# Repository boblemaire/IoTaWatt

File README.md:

### IotaWatt 4.8

See the [WiKi](https://github.com/boblemaire/IoTaWatt/wiki) for detailed information concerning installation and use of IoTaWatt. 

IoTaWatt forum is [here](https://community.iotawatt.com/)

IotaWatt is an open-hardware/open-source project to produce an accurate, low-cost, multi-channel, and easy to use electric power monitor.  It's based on the ESP8266 IoT platform using MCP3208 12 bit ADCs to sample voltage and current at high sample rates. As a datalogger the device has a real-time clock and SDcard and supports data querry with the integrated web server.

* monitors up to 14 circuits  
* Accuracy typically within 1%  
* Local SDcard stores up to 15 years worth of data.
* REST APIs to extract data
* Supports many different make, model and capacity current transformers  
* Supports generic definition of any current transformer  
* Three-phase capable  
* Local LAN browser based configuration  
* Local LAN browser based status display  
* Local LAN browser based graphing analytic tools  
* Open Hardware/Software 
* Upload to influxDB   
* Upload to [Emoncms.org](https://emoncms.org/)  
* Demo configuration app at [IoTaWatt.com](http://iotawatt.com)  

The software samples input channels at a rate of 35-40 channels per second, recording voltage(V), power(Watts), and energy(kWh) to the local SD card every five seconds.  The Emoncms browser based graphing utility can be used on the local WiFi network to view data or the data can be uploaded to an Emoncms server or an influxDB server. In the event of WiFi or internet service disruptions, the IotaWatt will continue to log locally and bulk update the server when WiFi is restored.

The basic configuration uses one voltage reference channel and fourteen current sense channels for monitoring up to fourteen single phase circuits.  Current sense channels may be used, with slight modification, as additional voltage/phase reference channels to allow monitoring of three-phase power systems.  There is also an option to estimate three phase power using a single voltage/phase reference.

The configuration and monitoring app runs on any browser based device that is connected to the local WiFi network. A demo is available at [iotawatt.com](http://iotawatt.com)

Thanks to contributors of other open software that have been incorporated into this project.  In particular the Emoncms, ArduinoJSON and SDWebServer software made a lot of this possible, not to mention the Arduino/ESP8266 project and related forums.

The [WiKi](https://github.com/boblemaire/IoTaWatt/wiki) is a work in progress and provides details of installation and use.

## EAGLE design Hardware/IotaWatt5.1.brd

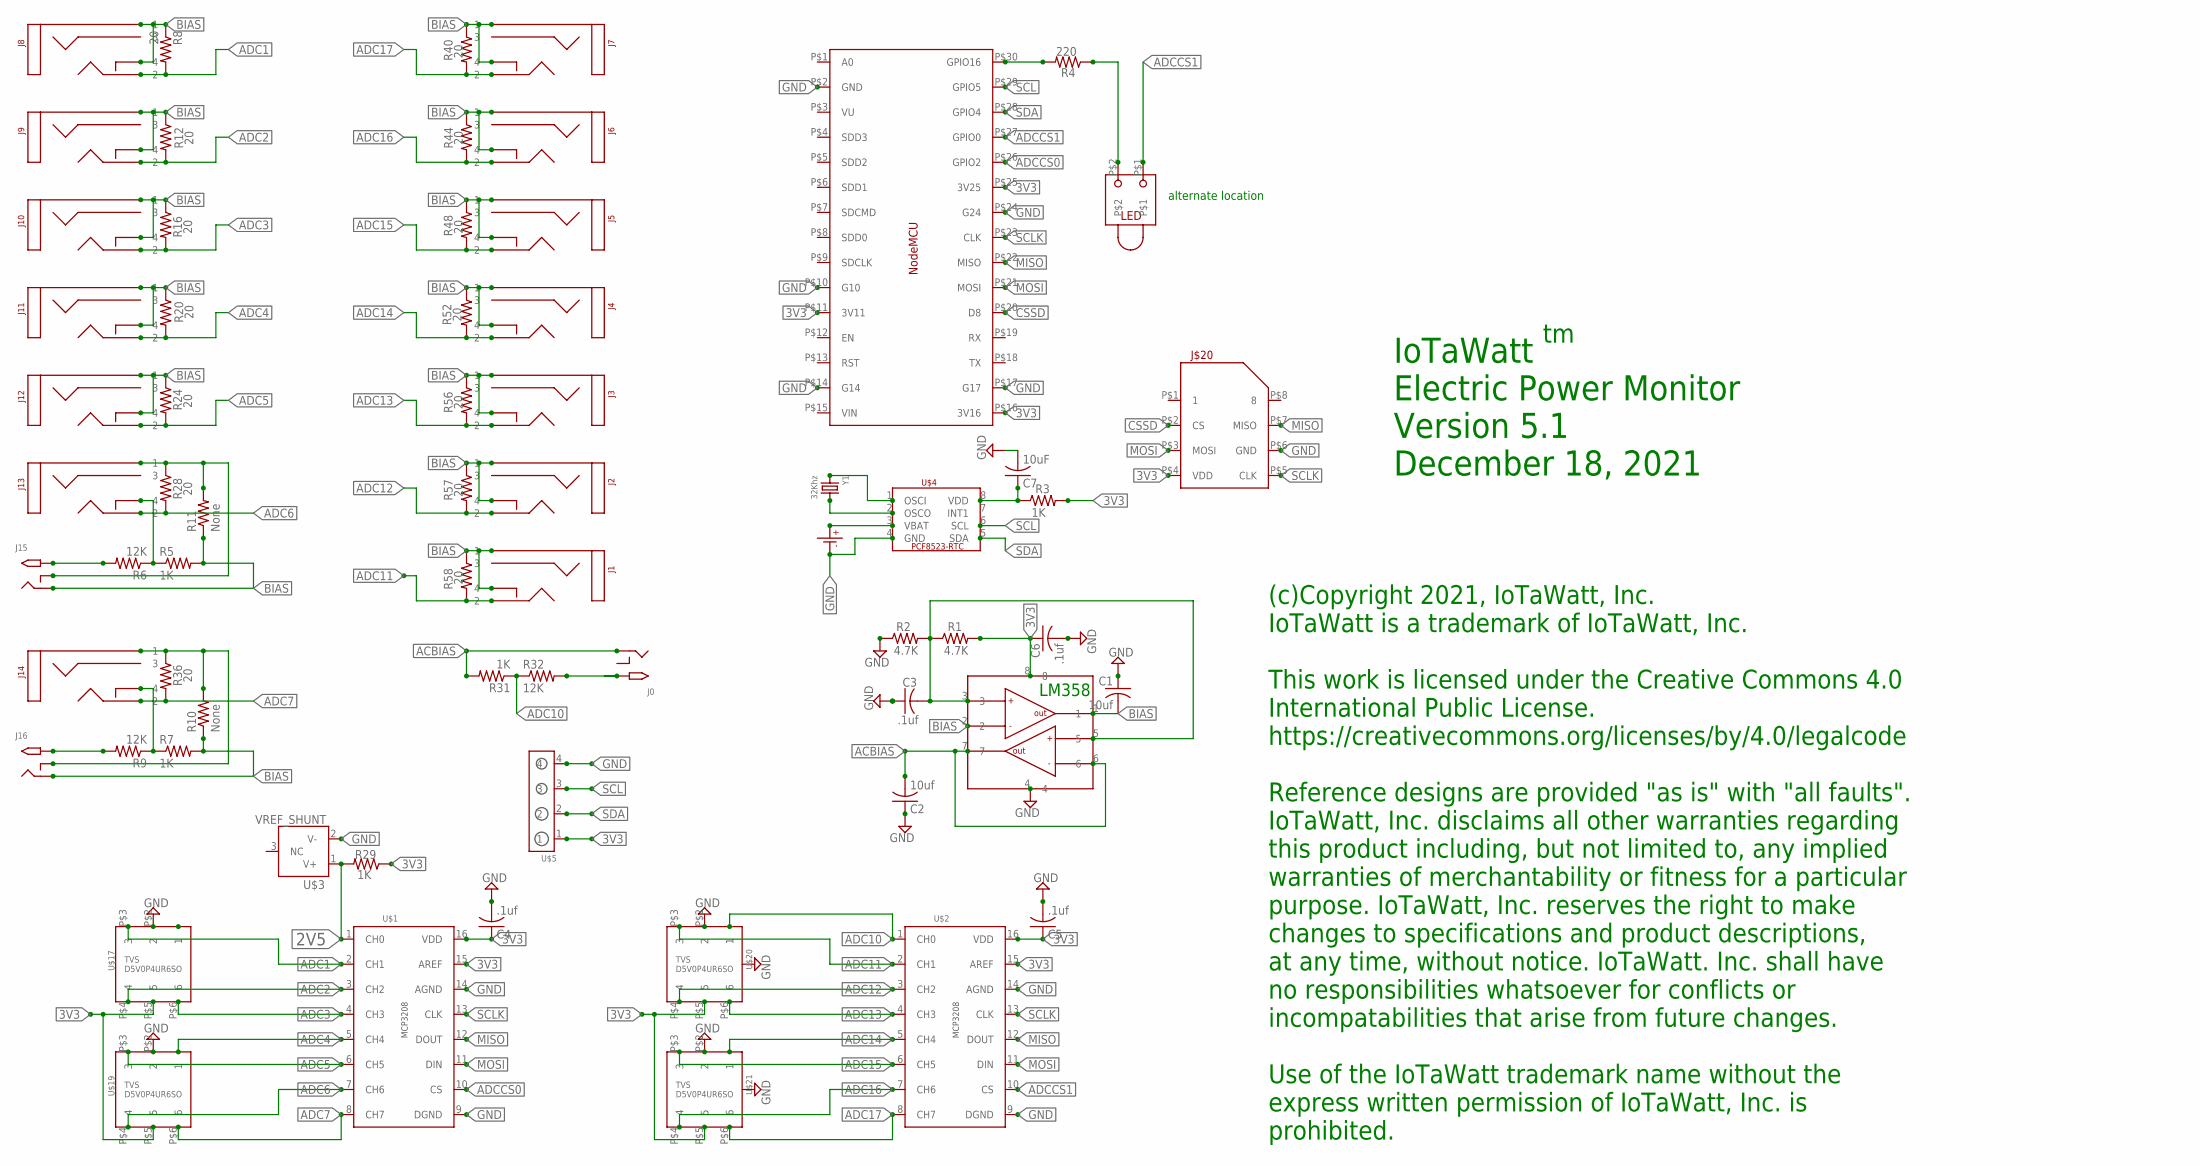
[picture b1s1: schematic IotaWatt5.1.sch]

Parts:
C1, C2: 10uf; C0805
C3, C4, C5, C6: .1uf; C0805
C7: 10uF; C0805
J0, J15, J16: 2.1MMJACKSMT; DCJACK_2MM_SMT
J1, J2, J3, J4, J5, J6, J7, J8, J9, J10, J11, J12, J13, J14: STEREO_SMD; STEREO_SMT
J$20: MICROSD_PUSH/PULL; MICROSD
R1, R2: 4.7K; R0805
R3, R5, R7, R29, R31: 1K; R0805
R4: 220; R0805
R6, R9, R32: 12K; R0805
R8, R12, R16, R20, R24, R28, R36, R40, R44, R48, R52, R56, R57, R58: 20; R0805
R10, R11: None; R0805
U$1, U$2: MCP3208; SOIC_16
U$3: VREF_SHUNT; SOT23_3
U$4: PCF8523_RTC; SOIC_8
U$5: HEADER_1X4
U$16: NODEMCU
U$17, U$19, U$20, U$21: TVS_4CHAN_ARRAYSC-74; SC-74
U$18: CR1220SMD
U$22: LM358_DUAL_OP-AMP; SOIC_8
U$23: LED_RT_TRH; LED_TH_RT
Y1: 32Khz; CRYSTAL_8X3.8

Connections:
2V5: R29.2, U$1.1 (CH0), U$3.1 (V+)
3V3: C4.1, C5.1, C6.1, J$20.P$4 (VDD), R1.2, R3.2, R29.1, U$1.15 (AREF), U$1.16 (VDD), U$2.15 (AREF), U$2.16 (VDD), U$5.1, U$16.P$11 (3V11), U$16.P$16 (3V16), U$16.P$25 (3V25), U$17.P$5 (5), U$19.P$5 (5), U$20.P$5 (5), U$21.P$5 (5), U$22.8
ACBIAS: C2.2, J0.GND (RING), R31.2, U$22.6, U$22.7
ADC1: J8.P$2 (2), R8.2, U$1.2 (CH1), U$17.P$3 (3)
ADC2: J9.P$2 (2), R12.2, U$1.3 (CH2), U$17.P$4 (4)
ADC3: J10.P$2 (2), R16.2, U$1.4 (CH3), U$17.P$6 (6)
ADC4: J11.P$2 (2), R20.2, U$1.5 (CH4), U$19.P$1 (1)
ADC5: J12.P$2 (2), R24.2, U$1.6 (CH5), U$19.P$3 (3)
ADC6: J13.P$2 (2), R28.2, U$1.7 (CH6), U$19.P$4 (4)
ADC7: J14.P$2 (2), R36.2, U$1.8 (CH7), U$19.P$6 (6)
ADC10: R31.1, R32.1, U$2.1 (CH0), U$20.P$1 (1)
ADC11: J1.P$2 (2), R58.2, U$2.2 (CH1), U$20.P$3 (3)
ADC12: J2.P$2 (2), R57.2, U$2.3 (CH2), U$20.P$4 (4)
ADC13: J3.P$2 (2), R56.2, U$2.4 (CH3), U$20.P$6 (6)
ADC14: J4.P$2 (2), R52.2, U$2.5 (CH4), U$21.P$1 (1)
ADC15: J5.P$2 (2), R48.2, U$2.6 (CH5), U$21.P$3 (3)
ADC16: J6.P$2 (2), R44.2, U$2.7 (CH6), U$21.P$4 (4)
ADC17: J7.P$2 (2), R40.2, U$2.8 (CH7), U$21.P$6 (6)
ADCCS0: U$1.10 (CS), U$16.P$26 (GPIO2)
ADCCS1: U$2.10 (CS), U$16.P$27 (GPIO0), U$23.P$1
BIAS: C1.2, J1.P$1 (1), J1.P$4 (4), J2.P$1 (1), J2.P$4 (4), J3.P$1 (1), J3.P$4 (4), J4.P$1 (1), J4.P$4 (4), J5.P$1 (1), J5.P$4 (4), J6.P$1 (1), J6.P$4 (4), J7.P$1 (1), J7.P$4 (4), J8.P$1 (1), J8.P$4 (4), J9.P$1 (1), J9.P$4 (4), J10.P$1 (1), J10.P$4 (4), J11.P$1 (1), J11.P$4 (4), J12.P$1 (1), J12.P$4 (4), J15.GND (RING), J16.GND (RING), R5.2, R7.2, R8.1, R10.1, R11.1, R12.1, R16.1, R20.1, R24.1, R40.1, R44.1, R48.1, R52.1, R56.1, R57.1, R58.1, U$22.1, U$22.2
CSSD: J$20.P$2 (CS), U$16.P$20 (D8)
GND: C1.1, C2.1, C3.1, C4.2, C5.2, C6.2, C7.2, J$20.P$6 (GND), R2.1, U$1.9 (DGND), U$1.14 (AGND), U$2.9 (DGND), U$2.14 (AGND), U$3.2 (V-), U$4.4 (GND), U$5.4, U$16.P$2 (GND), U$16.P$10 (G10), U$16.P$14 (G14), U$16.P$17 (G17), U$16.P$24 (G24), U$17.P$2 (2), U$18.P- (P$-), U$19.P$2 (2), U$20.P$2 (2), U$21.P$2 (2), U$22.4
MISO: J$20.P$7 (MISO), U$1.12 (DOUT), U$2.12 (DOUT), U$16.P$22 (MISO)
MOSI: J$20.P$3 (MOSI), U$1.11 (DIN), U$2.11 (DIN), U$16.P$21 (MOSI)
unnamed: C7.1, R3.1, U$4.8 (VDD)
unnamed: J15.PWR2 (TIP), R6.2
unnamed: J16.PWR2 (TIP), R9.2
unnamed: J14.P$1 (1), J16.GNDBREAK (RING_SW), R10.2, R36.1
unnamed: J13.P$1 (1), J15.GNDBREAK (RING_SW), R11.2, R28.1
unnamed: J14.P$4 (4), R7.1, R9.1
unnamed: R4.1, U$23.P$2
unnamed: J13.P$4 (4), R5.1, R6.1
unnamed: R4.2, U$16.P$30 (GPIO16)
unnamed: J0.PWR2 (TIP), R32.2
unnamed: U$4.3 (VBAT), U$18.P+ (P$+)
unnamed: U$4.2 (OSCO), Y1.P$4 (2)
unnamed: U$4.1 (OSCI), Y1.P$1 (1)
SCL: U$4.6 (SCL), U$5.3, U$16.P$29 (GPIO5)
SCLK: J$20.P$5 (CLK), U$1.13 (CLK), U$2.13 (CLK), U$16.P$23 (CLK)
SDA: U$4.5 (SDA), U$5.2, U$16.P$28 (GPIO4)
VREF: C3.2, R1.1, R2.2, U$22.3, U$22.5

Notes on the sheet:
IoTaWatt Electric Power Monitor Version 5.1 December 18, 2021
alternate location
LM358
(c)Copyright 2021, IoTaWatt, Inc. IoTaWatt is a trademark of IoTaWatt, Inc. This work is licensed under the Creative Commons 4.0 International Public License. https://creativecommons.org/licenses/by/4.0/legalcode Reference designs are provided "as is" with "all faults". IoTaWatt, Inc. disclaims all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

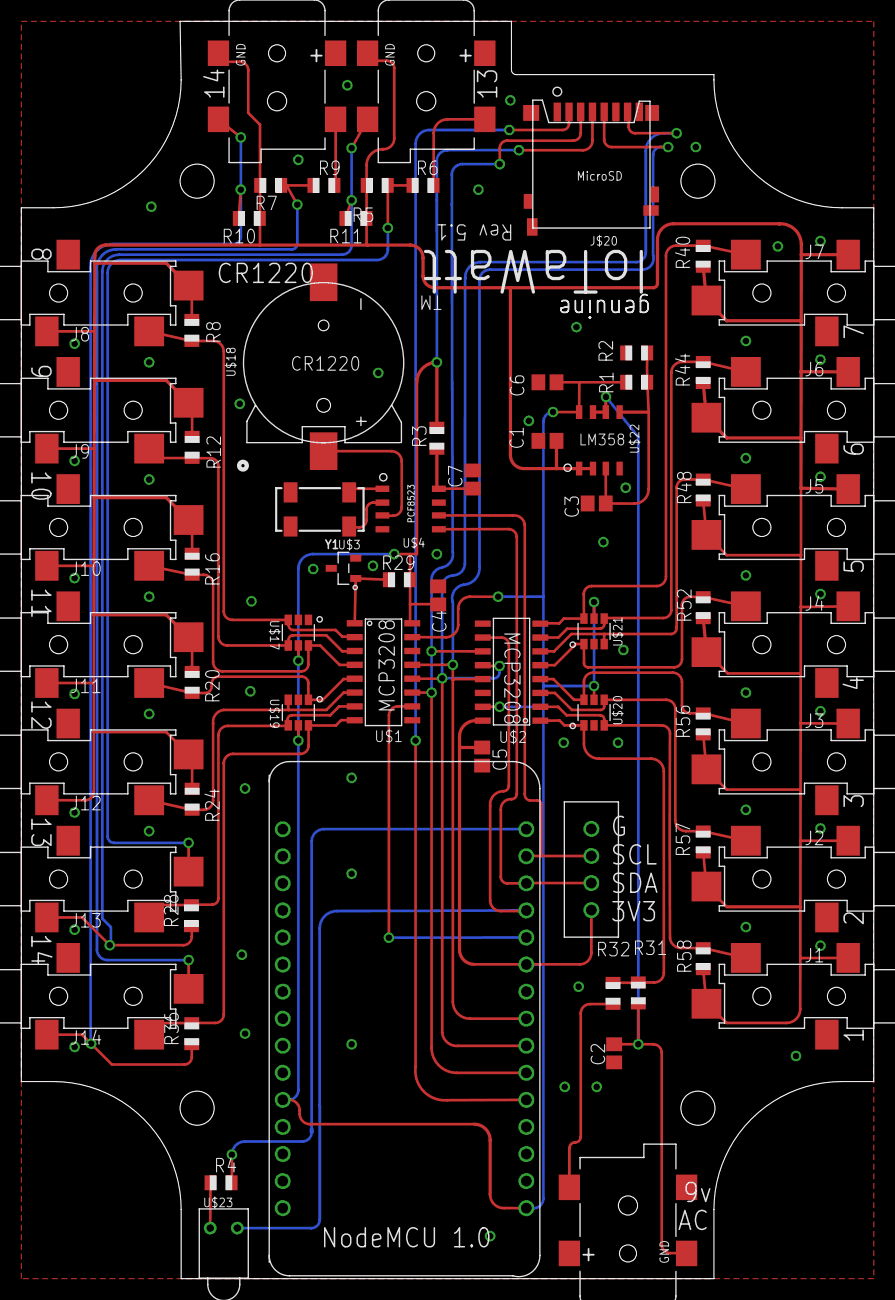
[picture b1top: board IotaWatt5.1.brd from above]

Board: 2 copper layers, 80.0 x 118.0 mm, 66 parts (0 on the bottom side), 42 nets.

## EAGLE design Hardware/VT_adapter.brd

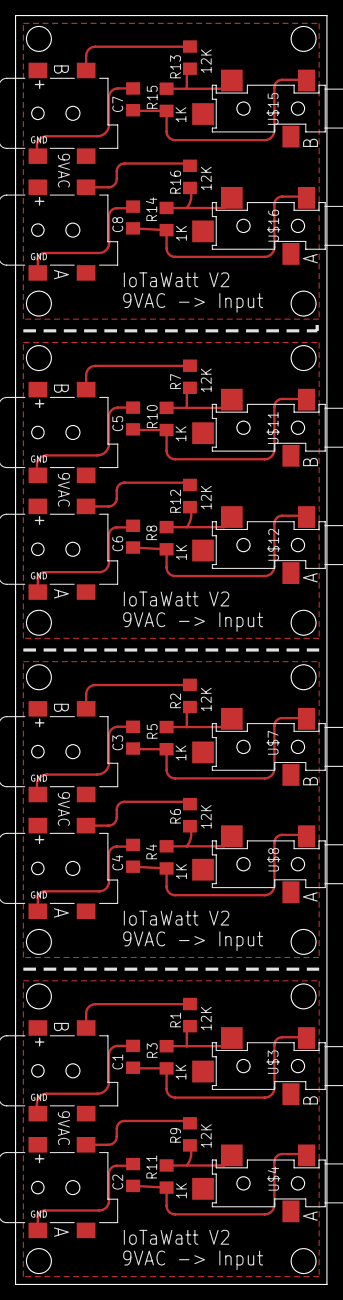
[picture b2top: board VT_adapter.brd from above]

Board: 2 copper layers, 40.0 x 163.0 mm, 40 parts (0 on the bottom side), 32 nets.

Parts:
C1, C2, C3, C4, C5, C6, C7, C8: 10uf; C1206
R1, R2, R6, R7, R9, R12, R13, R16: 12K; R1206
R3, R4, R5, R8, R10, R11, R14, R15: 1K; R1206
U$1, U$2, U$5, U$6, U$9, U$10, U$13, U$14: 2.1MMJACKSMT; DCJACK_2MM_SMT
U$3, U$4, U$7, U$8, U$11, U$12, U$15, U$16: STEREO_SMD; STEREO_SMT

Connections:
unnamed: C1.2, R3.2, U$3.P$1
unnamed: R1.2, R3.1, U$3.P$2
unnamed: C1.1, U$1.GND
unnamed: C2.1, U$2.GND
unnamed: R4.2, R6.2, U$8.P$2
unnamed: R1.1, U$1.PWR2
unnamed: R9.1, U$2.PWR2
unnamed: C4.2, R4.1, U$8.P$1
unnamed: C3.2, R5.2, U$7.P$1
unnamed: C3.1, U$5.GND
unnamed: R9.2, R11.2, U$4.P$2
unnamed: C2.2, R11.1, U$4.P$1
unnamed: R2.1, U$5.PWR2
unnamed: C4.1, U$6.GND
unnamed: R6.1, U$6.PWR2
unnamed: R2.2, R5.1, U$7.P$2
unnamed: R8.2, R12.2, U$12.P$2
unnamed: C6.2, R8.1, U$12.P$1
unnamed: C5.2, R10.2, U$11.P$1
unnamed: C5.1, U$9.GND
unnamed: R7.1, U$9.PWR2
unnamed: C6.1, U$10.GND
unnamed: R12.1, U$10.PWR2
unnamed: R7.2, R10.1, U$11.P$2
unnamed: R14.2, R16.2, U$16.P$2
unnamed: C8.2, R14.1, U$16.P$1
unnamed: C7.2, R15.2, U$15.P$1
unnamed: C7.1, U$13.GND
unnamed: R13.1, U$13.PWR2
unnamed: C8.1, U$14.GND
unnamed: R16.1, U$14.PWR2
unnamed: R13.2, R15.1, U$15.P$2

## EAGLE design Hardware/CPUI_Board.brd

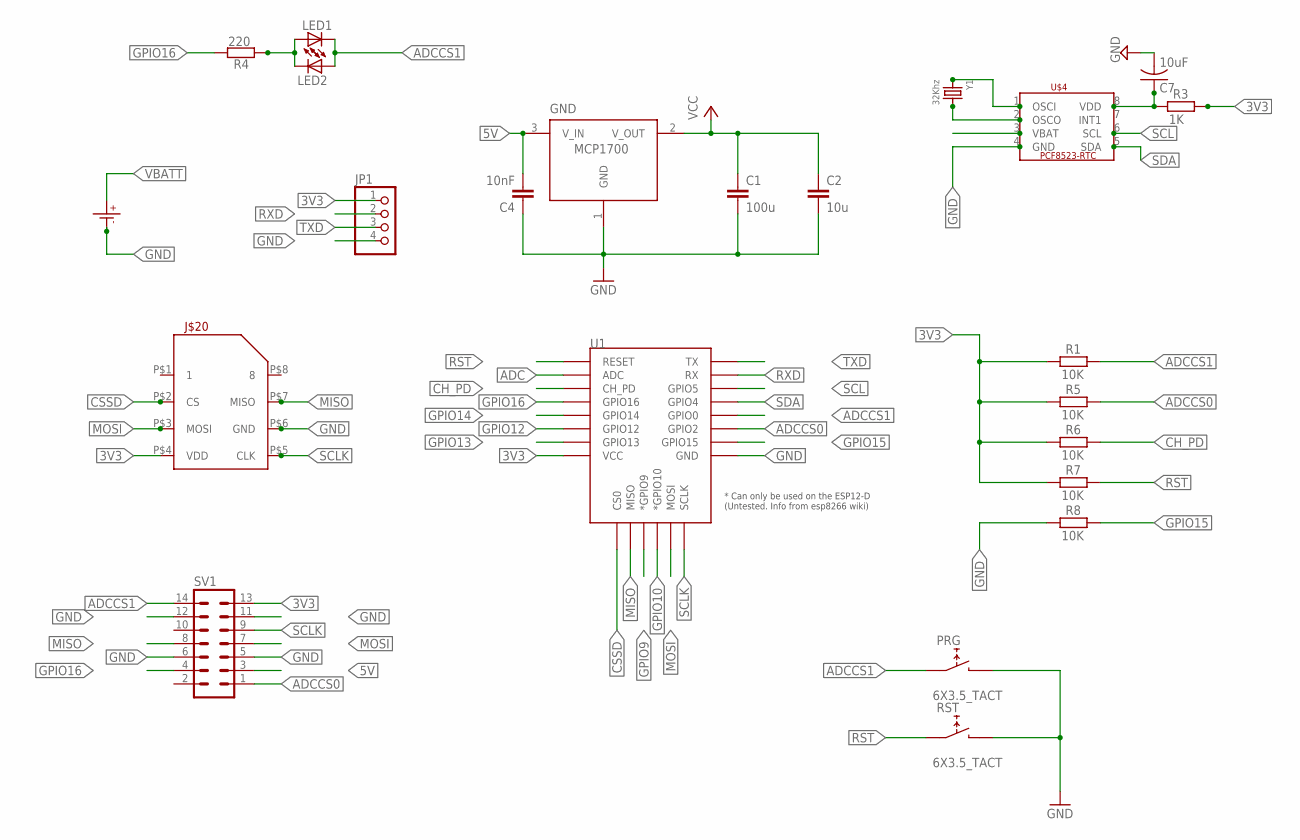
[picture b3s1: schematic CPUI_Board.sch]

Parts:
C1: 100u; C0805
C2: 10u; C0805
C4: 10nF; C0805
C7: 10uF; C0805
GND: MCP1700SOT23; SOT-23
J$20: MICROSD_PUSH/PULL; MICROSD
JP1: PINHD-1X4; 1X04
LED1, LED2: LEDCHIPLED_0805; CHIPLED_0805
PRG: 6X3.5_TACT; TACT_6X3.5
R1, R5, R6, R7, R8: 10K; R0805
R3: 1K; R0805
R4: 220; R0805
RST: 6X3.5_TACT; TACT_6X3.5
SV1: MA07-2
U1: ESP12ESMD; ESP12E-SMD
U$1: CR1220SMD
U$4: PCF8523_RTC; SOIC_8
Y1: 32Khz; CRYSTAL_8X3.8

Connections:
3V3: C1.1, C2.1, GND.2 (V_OUT), J$20.P$4 (VDD), JP1.1, R1.1, R3.2, R5.1, R6.1, R7.1, SV1.13, U1.VCC
5V: C4.2, GND.3 (V_IN), SV1.3
ADC: U1.ADC
ADCCS0: R5.2, SV1.1, U1.GPIO2
ADCCS1: LED1.C, LED2.A, PRG.P$1 (1), R1.2, SV1.14, U1.GPIO0
CH_PD: R6.2, U1.CH_PD
CSSD: J$20.P$2 (CS), U1.CS0
GND: C1.2, C2.2, C4.1, C7.2, GND.1 (GND), J$20.P$6 (GND), JP1.4, PRG.P$2 (2), R8.1, RST.P$2 (2), SV1.5, SV1.6, SV1.11, SV1.12, U1.GND, U$1.P- (P$-), U$4.4 (GND)
GPIO9: U1.GPIO9 (*GPIO9)
GPIO10: U1.GPIO10 (*GPIO10)
GPIO12: U1.GPIO12
GPIO13: U1.GPIO13
GPIO14: U1.GPIO14
GPIO15: R8.2, U1.GPIO15
GPIO16: R4.2, SV1.4, U1.GPIO16
MISO: J$20.P$7 (MISO), SV1.8, U1.MISO
MOSI: J$20.P$3 (MOSI), SV1.7, U1.MOSI
unnamed: C7.1, R3.1, U$4.8 (VDD)
unnamed: LED1.A, LED2.C, R4.1
unnamed: U$4.2 (OSCO), Y1.P$4 (2)
unnamed: U$4.1 (OSCI), Y1.P$1 (1)
RST: R7.2, RST.P$1 (1), U1.RESET
RXD: JP1.2, U1.RXD0 (RX)
SCL: U1.GPIO5, U$4.6 (SCL)
SCLK: J$20.P$5 (CLK), SV1.9, U1.SCLK
SDA: U1.GPIO4, U$4.5 (SDA)
TXD: JP1.3, U1.TXD0 (TX)
VBATT: U$1.P+ (P$+), U$4.3 (VBAT)

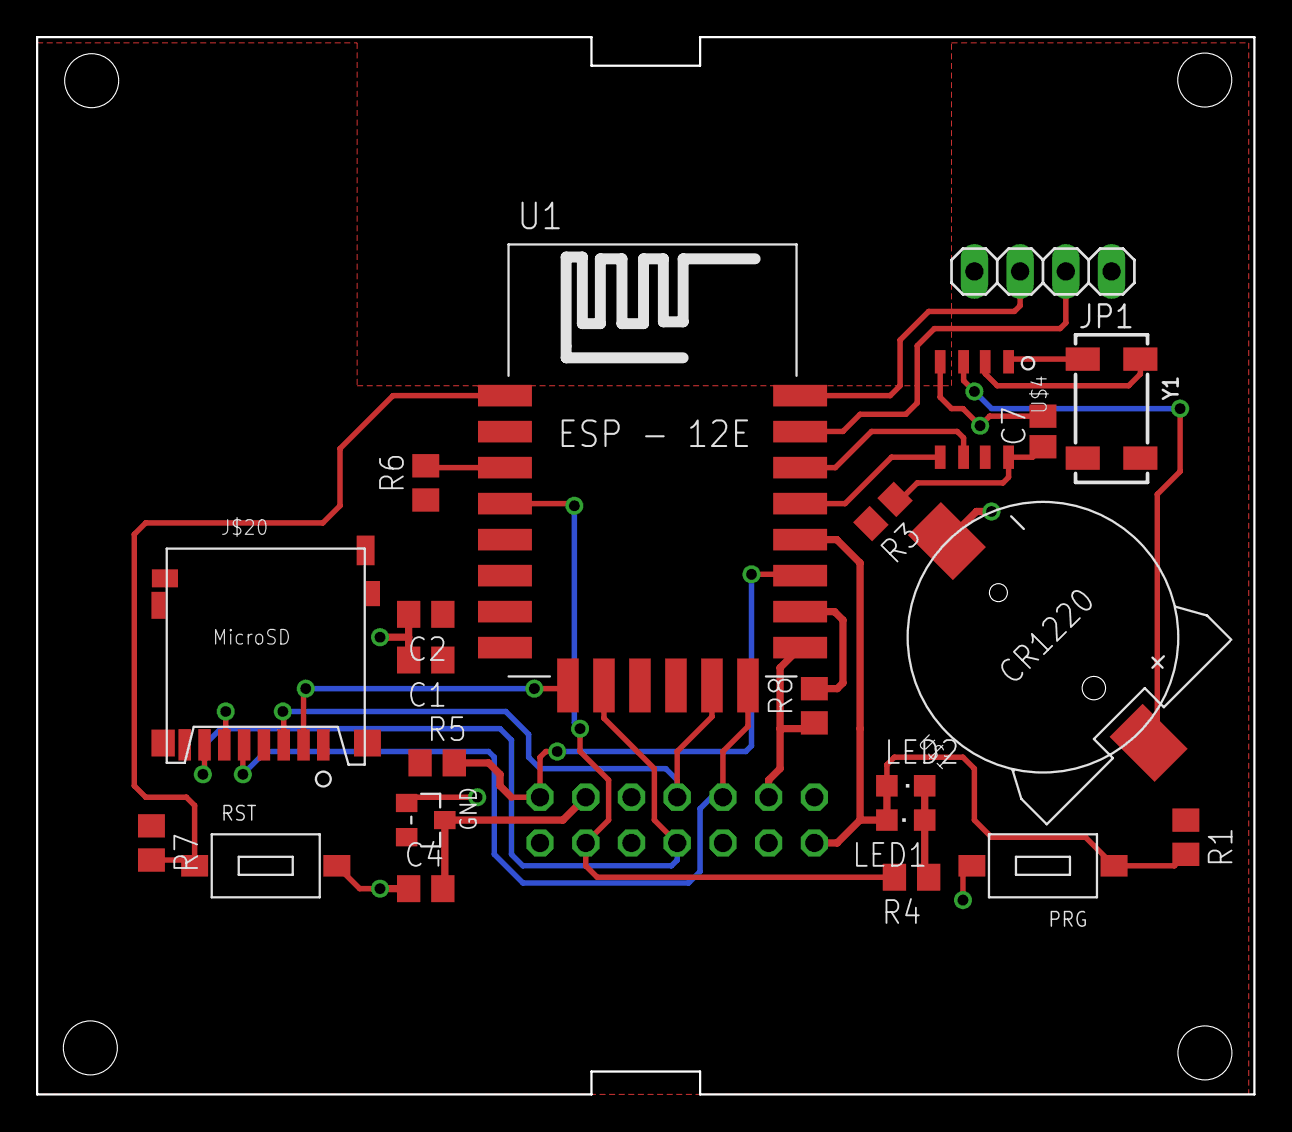
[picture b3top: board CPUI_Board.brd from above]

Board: 2 copper layers, 67.6 x 58.7 mm, 23 parts (1 on the bottom side), 22 nets.

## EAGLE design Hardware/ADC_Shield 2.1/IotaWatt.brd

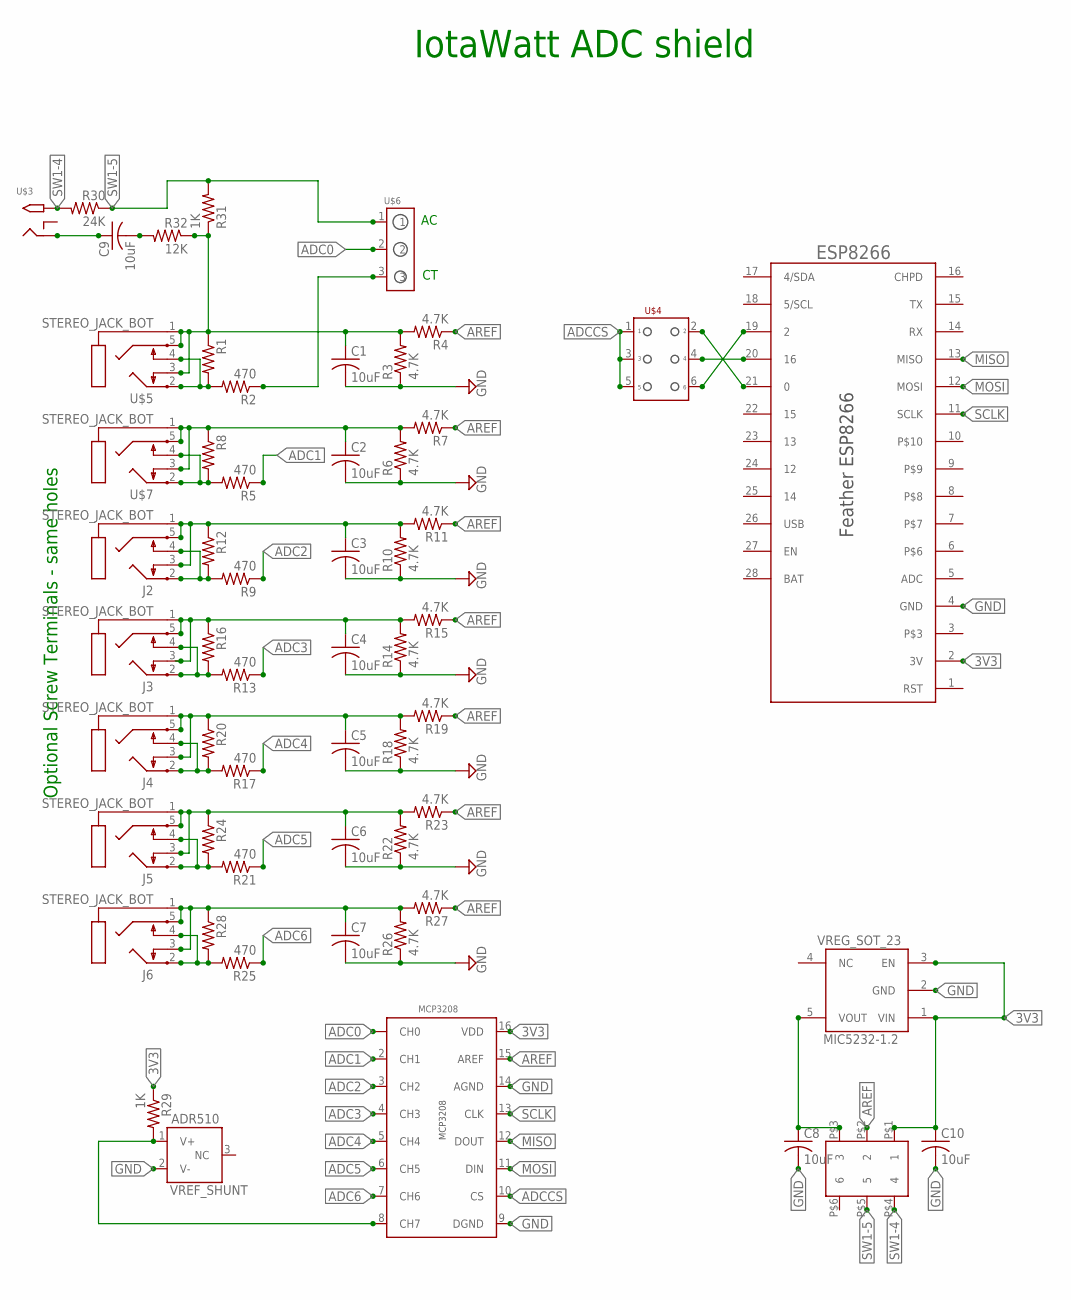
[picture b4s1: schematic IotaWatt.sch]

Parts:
ADR510: VREF_SHUNT; SOT23_3
C1, C2, C3, C4, C5, C6, C7, C8, C9, C10: 10uF; C0805
J2, J3, J4, J5, J6: STEREO_JACK_BOT; STX3100
MCP3208: MCP3208; SOIC_16
MIC5232-1.2: VREG_SOT_23; SOT23_5
R1, R8, R12, R16, R20, R24, R28: R-US_FLIPFLOP7; 0805-THM-7
R2, R5, R9, R13, R17, R21, R25: 470; R0805
R3, R4, R6, R7, R10, R11, R14, R15, R18, R19, R22, R23, R26, R27: 4.7K; R0805
R29, R31: 1K; R0805
R30: 24K; R0805
R32: 12K; R0805
U$1: ESP8266FEATHER; FEATHERWING
U$3: 2.1MMJACKBOTTHM; PJ-102A-BOT
U$4: HEADER_2X3
U$5, U$7: STEREO_JACK_BOT; STX3100
U$6: HEADER_1X3
U$8: DPDT_SMT_SW; JS202011SCQN

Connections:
3V3: C10.1, MCP3208.16 (VDD), MIC5232-1.2.1 (VIN), MIC5232-1.2.3 (EN), R29.1, U$1.2 (3V), U$8.P$1 (1)
ADC0: MCP3208.1 (CH0), U$6.2
ADC1: MCP3208.2 (CH1), R5.1
ADC2: MCP3208.3 (CH2), R9.1
ADC3: MCP3208.4 (CH3), R13.1
ADC4: MCP3208.5 (CH4), R17.1
ADC5: MCP3208.6 (CH5), R21.1
ADC6: MCP3208.7 (CH6), R25.1
ADC7: ADR510.1 (V+), MCP3208.8 (CH7), R29.2
ADCCS: MCP3208.10 (CS), U$4.1, U$4.3, U$4.5
AREF: MCP3208.15 (AREF), R4.1, R7.1, R11.1, R15.1, R19.1, R23.1, R27.1, U$8.P$2 (2)
GND: ADR510.2 (V-), C1.2, C2.2, C3.2, C4.2, C5.2, C6.2, C7.2, C8.2, C10.2, MCP3208.9 (DGND), MCP3208.14 (AGND), MIC5232-1.2.2 (GND), R3.1, R6.1, R10.1, R14.1, R18.1, R22.1, R26.1, U$1.4 (GND)
MISO: MCP3208.12 (DOUT), U$1.13 (MISO)
MOSI: MCP3208.11 (DIN), U$1.12 (MOSI)
unnamed: R2.1, U$6.3
unnamed: C1.1, R1.1, R3.2, R4.2, R31.1, R32.1, U$5.1, U$5.3 (4), U$5.5 (2)
unnamed: U$1.21 (0), U$4.2
unnamed: C2.1, R6.2, R7.2, R8.1, U$7.1, U$7.3 (4), U$7.5 (2)
unnamed: J2.2 (5), J2.4 (3), R9.2, R12.2
unnamed: U$1.19 (2), U$4.6
unnamed: U$1.20 (16), U$4.4
unnamed: R1.2, R2.2, U$5.2 (5), U$5.4 (3)
unnamed: C3.1, J2.1, J2.3 (4), J2.5 (2), R10.2, R11.2, R12.1
unnamed: C5.1, J4.1, J4.3 (4), J4.5 (2), R18.2, R19.2, R20.1
unnamed: J5.2 (5), J5.4 (3), R21.2, R24.2
unnamed: C6.1, J5.1, J5.3 (4), J5.5 (2), R22.2, R23.2, R24.1
unnamed: C9.2, R32.2
unnamed: J6.2 (5), J6.4 (3), R25.2, R28.2
unnamed: C7.1, J6.1, J6.3 (4), J6.5 (2), R26.2, R27.2, R28.1
unnamed: R5.2, R8.2, U$7.2 (5), U$7.4 (3)
unnamed: J3.2 (5), J3.4 (3), R13.2, R16.2
unnamed: C4.1, J3.1, J3.3 (4), J3.5 (2), R14.2, R15.2, R16.1
unnamed: C8.1, MIC5232-1.2.5 (VOUT), U$8.P$3 (3)
unnamed: J4.2 (5), J4.4 (3), R17.2, R20.2
unnamed: C9.1, U$3.RING
SCLK: MCP3208.13 (CLK), U$1.11 (SCLK)
SW1-4: R30.2, U$3.TIP, U$8.P$4 (4)
SW1-5: R30.1, R31.2, U$6.1, U$8.P$5 (5)

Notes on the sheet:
IotaWatt ADC shield
Optional Screw Terminals - same holes

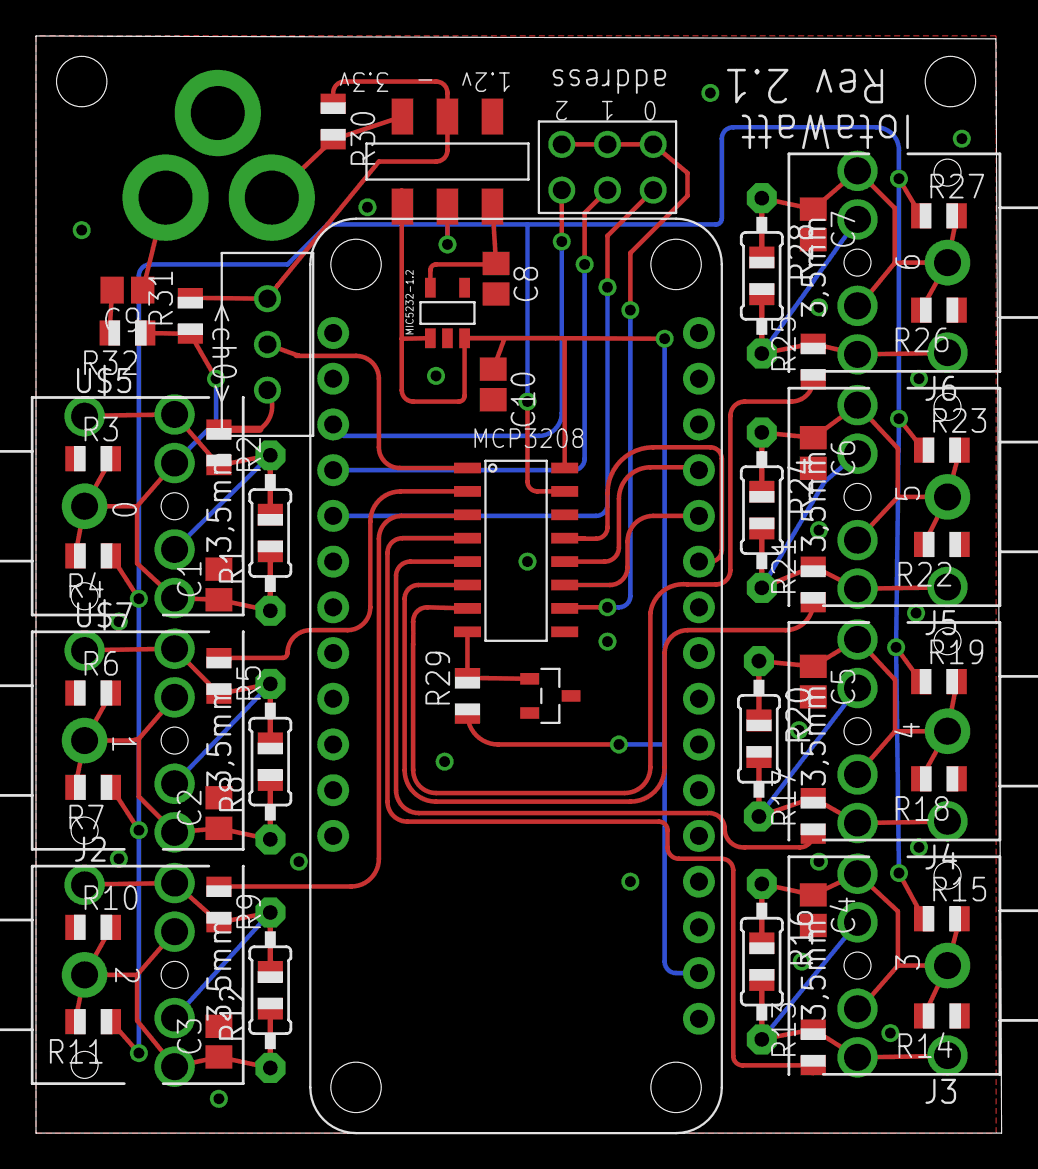
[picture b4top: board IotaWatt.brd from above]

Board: 2 copper layers, 53.6 x 61.0 mm, 57 parts (0 on the bottom side), 38 nets.

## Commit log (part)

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2020-03-09 Allow duplicate measurement names in influxDB
2020-03-10 Restart after power-fail no AP connect.
    WiFimanager leaves WiFi in state where it will not autoconnect if WiFi becomes available. Restart after running WiFimanager to allow autoconnecvt when if or when WiFi is available.
2020-03-17 Add dotlocal
2020-03-20 Add scriptset.sort
    Adde method to sort a scriptset
2020-03-27 Use legacy mDNS
    2.6 core introduced a new implimentation of mDNS using a DNS-SD class. It doesn't seem to work, sometimes failing the begin() method, and when succeeding, doesn't seem to work.
2020-03-27 Remove inactive code
2020-03-27 Sort outputs
2020-03-27 Remove diagnostic print
2020-03-28 Allow for varying log record size
    Record size was fixed at 256. Now length is specified when the log is instantiated.
2020-03-29 Organizational changes
    Change file path declarations to #define "string"
    Change various global variables to a new convention of starting name with upper-case letter.
    In progress export_log module which started all this
2020-04-02 Version 02_05_07
    Fixes problem with https:// Emoncms url that was introduced by changes to asyncHTTPrequest after release 02_05_02.
2020-04-03 Add export log
    Export log keeps track of import and export as defined by a script (+/-) output and saves the totals in a discrete log. Have not yet figured out how to make that accessible so no user interface yet. 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
    This effort also introduced changes in how log files are defined and introduces a gl;obal naming convention where globals start with a capital letter.
2020-04-12 Add VAR, VARh to outputs and query
    Also made extended sum to sum/interval and report Ah, VAh in addition to previous Wh
2020-04-20 Add AccuEnergy CTs
2020-04-23 Ignore '/' URI
    Not technically correct but to preserve compatability with previous releases
2020-04-30 make logWDT local
    Was a global
2020-04-30 Go through normal wait after failed download
    Stop repeated downloads
2020-04-30 Include retention policy in last post query
2020-05-01 Update copyright year to 2020 to provide "up to date" appearance
    would be factually correct since there commits this year ;-)
2020-05-01 [DATALAD RUNCMD] RF: make all images have consistent .png not .PNG extension
    === Do not change lines below ===
    {
    "chain": [],
    "cmd": "bash -c 'git-sedi \"\\.PNG\" \"\\.png\" && for f in */pics/{{,*/}}*.PNG; do git mv $f ${{f//.PNG/.png}}; done'",
    "exit": 0,
    "extra_inputs": [],
2020-05-01 Correct download filesize
2020-05-02 Update Query - add VAR and VARh
2020-05-03 PIO core 2.4.0
2020-05-06 Add more pre-defined time periods
2020-05-31 Corrected a lot of the inconsistent formatting, trailing whitespace and inconsistent indentation in graph 2
2020-05-31 Fixed a bug where the saved graph was deselected
2020-05-31 Lite mode can now be enabled via the query string parameter "lite_mode_graph", which selects a saved graph, enabled auto refresh and hides all of the controls
2020-06-04 Mostly auto-formatted the graph files with some manual formatting within the graph2 files to clean up the areas which aren't fixed automatically
2020-06-05 Fixed a bug within graph2 where the path debugging variable could not be used due to inconsistent trailing slash expectations in the ajax calls
2020-06-09 Reformat to VS-Code JS-CSS-HTML Formatter
    Lacking a standard, use defaults except indent set to 2.
2020-06-10 Document query parms and refresh/freeze
2020-06-11 Fix onload function call
2020-06-12 basic documentation for change password
2020-08-04 Add wifi status tab
2020-09-15 Bump version to 02_05_10
    Added Wifi status query and tables additions
2020-11-21 Fix chunked query response
    Webserver implied chunk handling was adding extra trailing 0 chunk. Changed over to using webserver chunking with sendContent. Fixes node-red parsing issue.
2020-11-22 Fix handling of decimal point after zero
2020-11-25 Set viewport meta tag 10 index.html
2020-11-25 Add p60 to Ideal 77DE-06-09(EU)
2020-12-02 Version 02_05_12
2020-12-05 Add limit
2021-01-25 Upload working no query yet
2021-02-01 Preliminary support for influxDB_v2
2021-02-04 Add HTTPSproxy
2021-02-06 influx1 and influx2 complete
2021-02-07 Update outputs.rst
    Hello Bob,
    I couldn't find anything on MAX and MIN in the documentation and kept on getting it mixed up in my own head.
    Hopefully the above is a) correct and b) helps explain MAX and MIN while providing a useful example.
    I don't know how to do photos (e.g. the func button)
2021-02-07 improve start/stop and config upload
2021-02-12 Issue #287, change /status content type to application/Json
2021-02-16 Reduce startup delay
2021-02-16 Add integration logs and reformat
2021-02-17 Add integrations ScriptSet
2021-02-17 Configure integrations
2021-02-17 Class to instantiate integrations with intergator Service
2021-02-17 Upgrade to core ESP8266/arduino core 2.6.3
2021-02-18 Update config hash in setConfig
2021-02-22 Add write cache
2021-02-22 Add integrations
2021-02-22 Set SD SPI speed to 25MHz - not sure this actually works
2021-03-01 Fix compile warning
2021-03-01 Changes for 3.0 core
2021-03-04 Initialize Scriptsets
2021-03-04 SDspi to 40Mhz
2021-03-05 Cleanup a bit - no functional changes
2021-03-05 Fix masterPhaseTable to recognize duplicates
2021-03-05 Adapt to ms scheduler
2021-03-05 remove integrations
2021-03-06 Add default port 8086
2021-03-06 Use HTTPOS proxy when available
2021-03-06 Suppress unnecessary message when stopped
2021-03-06 Do status like other uploaders
2021-03-07 PVoutput status
2021-03-07 Fix status message
2021-03-10 Update docs for 02_06_00
    Add uploaders
    add HTTPSproxy
    General review and update
    Move pics to individual folders by rst page
2021-03-10 Reissue failed query
2021-03-12 Restrict buffer use with many uploaders
2021-03-12 Restrict buffer use with multiple uploaders
2021-03-13 No status update when no PVoutput
2021-03-16 Return false on url=null
2021-03-17 Initialize bucket
2021-03-17 Handle unspecified measurement, bucket, tokens
2021-03-18 Fail if type != emoncms (reboot problem)
2021-03-18 Reject HTTPS if proxy server not set
2021-03-20 reformat uploader specifications
2021-03-20 Reformat log message
2021-03-20 Version 02_06_02
2021-03-20 Update default config
    Set burdens to 20, remove "server" none, Set default VT to Jameco L6
2021-03-20 Improve query error recovery
2021-04-10 Update M9233 model
2021-05-03 Add semantic version utilities
2021-05-05 Adjust bingo time
2021-05-05 version 02_06_03
2021-05-05 Add password setup
2021-05-05 Add critical file protection
2021-05-07 Show mfg of VTs
2021-06-04 Change default config.txt to use JW-95001-NA VT
2021-06-04 Version 0.0.2
    Change JW-95001-NA cal
2021-06-17 Suppress recovered http messages
2021-06-22 Identify local vs remote access
2021-07-03 Tables.txt version 0.0.3
2021-07-08 Version 02_06_05
2021-08-18 Add log preformat
    Preformat log ahead to reduce SDcard wear.
2021-08-23 fix small typo
2021-09-03 Update index.htm
    slightly more specific GUI prompt for InfluxDB v2 Organization ID
2021-09-08 Add simple cache capability to integrator->run
2021-09-14 Extract JS from page
2021-09-15 Eliminate extra table downloads
2021-09-15 Add Integrations
    Complete, pre-testing merge
2021-09-16 Version 00.07.00
    Add integrations
2021-09-25 Add support for alternate RTC
2021-09-25 Revert device name message
2021-09-25 Reject invalid Script more gracefully
    Needed to allow regression from version 02_07_00+ which will have new tokens for integrations and virtual inputs. Scripts containing invalid tokens are logged and will return zero when run.
2021-09-27 Version 02_06_06
2021-09-29 Add simSolar
2021-09-29 Must be synchronized to use
2021-09-30 Fix create first integration
    Fix create first integration
2021-10-01 Fix influx uploaders delete
2021-10-05 Improve integration handling
2021-10-05 Correct version numbers in notes
2021-10-19 Add callbacks to historyLog and integrations
    When historylog and integrations are synchronized, they will write new records as appropriate, insuring they are updated as an atomic operation and precluding race conditions that rely on currency.
2021-10-19 Reformat integration log record to factor of blocksize (no span)
2021-10-20 Add confirm to delete integration
2021-10-26 Convert integrations to integrators
2021-10-31 Add more detailed trace
2021-10-31 Integrators documentation
2021-11-01 Still trying to fix this
2021-11-01 Edit
2021-11-02 Version 02_07_03
2021-11-05 Fix influx tag add/edit
2021-11-14 Modify flux query, issue #319
2021-11-14 Remove diagnostic message
2021-12-16 Show I2C address of clock
2021-12-16 Fix various Script problems
    Hz not reported correctly.
    Volts and Amps not correct in doubled or phase-phase in derived reference.
    Second and subsequent integrations returning zero.
2022-01-03 Show influx msg on failure
2022-01-05 Update RTC.cpp
    * Fixed typos
    * Refactored code
    * Range check the 2nd digit in y2d()
2022-01-07 Simplify and reduce code size.
2022-01-08 Fix build.
2022-02-12 Change heap trace from average to current
2022-03-05 Change pic
2022-03-15 Improve error reporting.
2022-03-25 Discontinue use of Legacy mDNS
    Problems associated with KASA App causing crashes.
2022-03-30 Increase maximum response value length
2022-04-09 prometheus scrape endpoint, no auth
2022-04-13 Fix exception in unencrypted error response
2022-04-13 Compatibility with core 3.2.0
2022-04-20 Fix yearly grouping
2022-04-27 Use assigned Vchan for sample
2022-04-27 Detect no voltage before first cross
2022-05-04 Remove old inactive code
2022-05-06 Fix time_t no longer uint32_t
2022-07-12 Update index.htm
    Updated the (i) icon with a different unicode character so it would be more cross os friendly.
2022-09-16 Add support for Prometheus Open Metrics format
2022-09-30 Change info symbol to unicode
2022-09-30 PIO update for 3.0.2 core
2022-12-04 Remove old test comments
2022-12-19 Regress to older MDNS
    Core 2.4.0 mdns
2022-12-19 Slow down SPI if SDcard init fails
2022-12-20 Version 02_08_01
    Interim version with core 2.4.0 to mitigate SD card issues
2023-01-18 fixing firefox issues
2023-01-25 Version 02_08_02
    Fix mDNS when AP changes
2023-02-17 Update VTconfig.rst
    Fixing spelling mistake.
2023-02-17 Update CTbasics.rst
    Fixing spelling
2023-05-01 Fix config version check on save
    When saving a config, send hash of basis config to insure updating current config, i.e. no other updates since basis copy was taken.
2023-09-19 Modify default config
    VT Jameco 112336
2023-12-17 Add github action to codespell master on push and PRs
2023-12-17 [DATALAD RUNCMD] run codespell throughout but ignore fail
    === Do not change lines below ===
    {
    "chain": [],
    "cmd": "codespell -w || :",
    "exit": 0,
    "extra_inputs": [],
2024-01-16 Bump readthedocs-sphinx-search from 0.1.0 to 0.3.2 in /Docs
    Bumps [readthedocs-sphinx-search](https://github.com/readthedocs/readthedocs-sphinx-search) from 0.1.0 to 0.3.2.
    - [Changelog](https://github.com/readthedocs/readthedocs-sphinx-search/blob/main/CHANGELOG.rst)
    - [Commits](https://github.com/readthedocs/readthedocs-sphinx-search/compare/0.1.0...0.3.2)
    ---
    updated-dependencies:
    - dependency-name: readthedocs-sphinx-search
2024-05-27 Update CTbasics.rst -- fix typo
2024-07-31 Assume + in time argument modifier
2025-04-02 Release 02_08_04
2025-08-25 fixed the dependencies
2025-10-17 Upgrade to Crypto 0.4.0
2025-10-17 Remove include CBC.h
2025-10-18 Make includes case sensitive
2025-10-21 Use Operator Foundation Crypto fork
2025-11-05 Move trace to separate module (from loop)
2025-11-05 Initialize uploader registry (stop on exception - temp)
2025-11-05 Uploaders moved to uploaders directory
2025-11-05 Move to uploaders directory and use uploader registry
2025-11-05 New module to facilitate Uploader class uploaders
2025-11-05 Uploader harmonization (#360)
    * Move trace to separate module (from loop)
    * Move trace and remove uploader includes
    * Initialize uploader registry (stop on exception - temp)
    * Uploaders moved to uploaders directory
    * Remove uploader pointers
    * Move to uploaders directory and use uploader registry
2025-11-07 Add HTTPGet support
2025-11-07 Add exception decoder
2025-11-07 Clean up unused declarations
2025-11-10 Uploader status as array
2025-11-11 Cleanup
2025-11-19 Fix case error on includes
2025-11-20 Fix case sensitive includes
2025-11-20 revert whitespace changes in index.htm

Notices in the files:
parts and their libraries:
microbuilder: This work is placed in the public domain, and may be freely used for commercial and non-commercial work with the following conditions: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
